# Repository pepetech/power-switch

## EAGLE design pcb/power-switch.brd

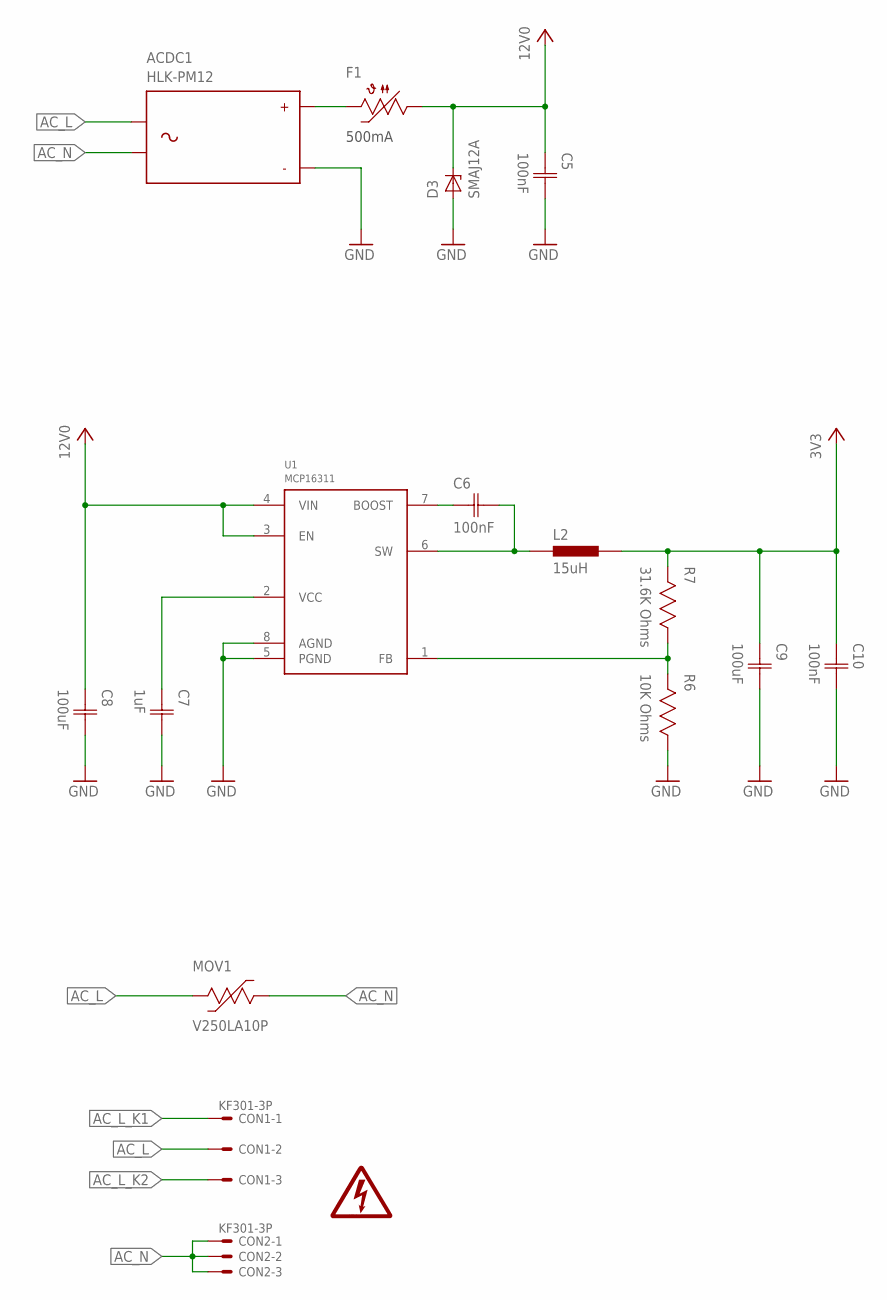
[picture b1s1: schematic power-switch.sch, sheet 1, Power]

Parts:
ACDC1: HLK-PM12
C5, C6, C10: 100nF; CAP0603
C7: 1uF; CAP0603
C8, C9: 100uF; CAP1206
CON1, CON2: KF301-3P
D3: SMAJ12A; DO214AC
F1: 500mA Hold; 1812
L2: 15uH; IND2520
LOGO1: HV_WARNING
MOV1: V250LA10P; VXXXLA10P
R6: 10K Ohms; RES0603
R7: 31.6K Ohms; RES0603
U1: MCP16311; MSOP8

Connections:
3V3: C9.1 (C1), C10.1 (C1), L2.2, R7.2; also elsewhere on the board
12V0: C5.1 (C1), C8.1 (C1), D3.C, F1.1, U1.3 (EN), U1.4 (VIN); also elsewhere on the board
AC_L: ACDC1.AC1, CON1.2, MOV1.2; also elsewhere on the board
AC_L_K1: CON1.1; also elsewhere on the board
AC_L_K2: CON1.3; also elsewhere on the board
AC_N: ACDC1.AC2, CON2.1, CON2.2, CON2.3, MOV1.1
GND: ACDC1.-VO, C5.2 (C2), C7.2 (C2), C8.2 (C2), C9.2 (C2), C10.2 (C2), D3.A, R6.1, U1.5 (PGND), U1.8 (AGND); also elsewhere on the board
unnamed: C6.2 (C2), L2.1, U1.6 (SW)
unnamed: ACDC1.+VO, F1.2
unnamed: C6.1 (C1), U1.7 (BOOST)
unnamed: C7.1 (C1), U1.2 (VCC)
unnamed: R6.2, R7.1, U1.1 (FB)

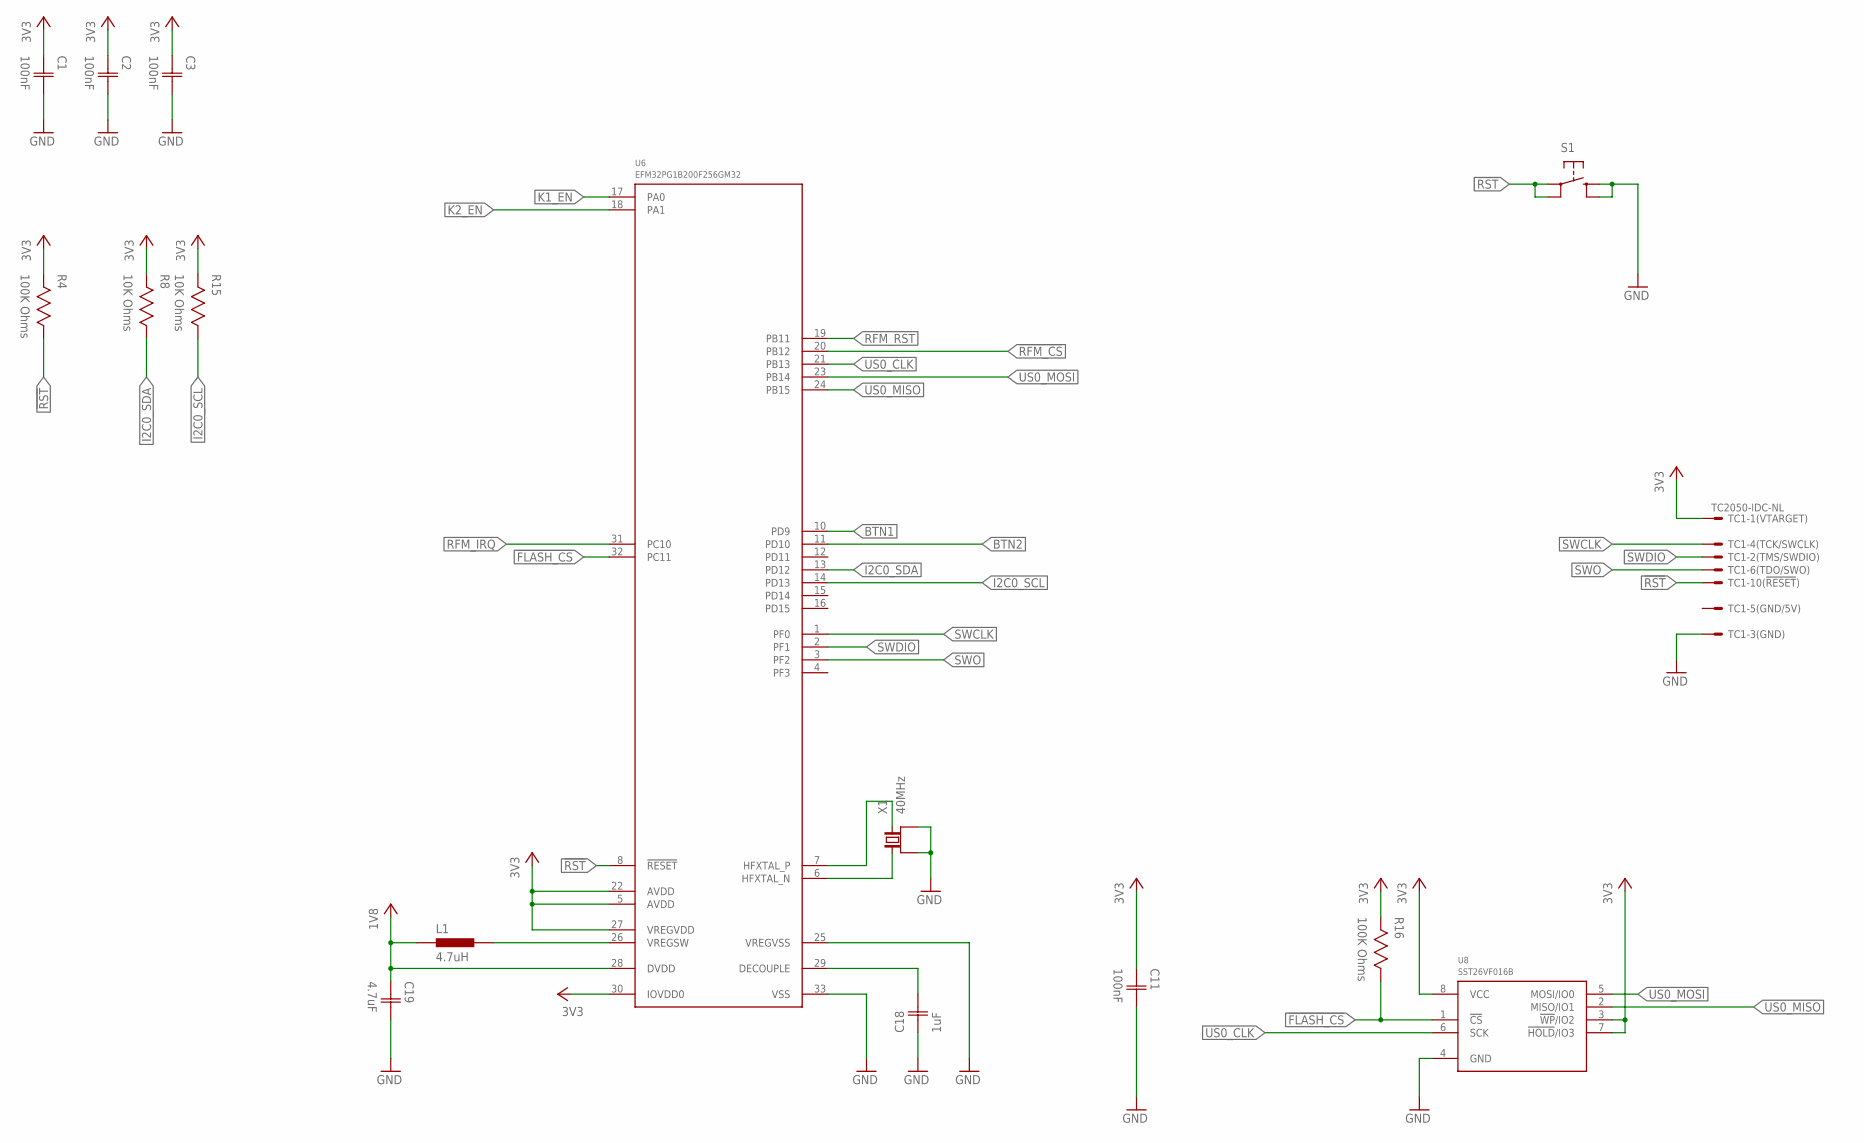
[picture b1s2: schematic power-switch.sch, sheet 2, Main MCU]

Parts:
C1, C2, C3, C11: 100nF; CAP0603
C18: 1uF; CAP0603
C19: 4.7uF; CAP0603
L1: 4.7uH; IND0603
R4, R16: 100K Ohms; RES0603
R8, R15: 10K Ohms; RES0603
S1: TAC_SWITCHSMD; TAC_SW_SMD_RESET
TC1: TC2050-IDC-NL
U6: EFM32PG1B200F256GM32; QFN32_0.5P
U8: SST26VF016B; WSOIC8
X1: 40MHz; 4-SMD-3225

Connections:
1V8: C19.1 (C1), L1.1, U6.28 (DVDD)
3V3: C1.1 (C1), C2.1 (C1), C3.1 (C1), C11.1 (C1), R4.2, R8.2, R15.2, R16.2, TC1.1, U6.5 (AVDD), U6.22 (AVDD), U6.27 (VREGVDD), U6.30 (IOVDD0), U8.3 (!WP!/IO2), U8.7 (!HOLD!/IO3), U8.8 (VCC); also elsewhere on the board
!FLASH_CS: R16.1, U6.32 (PC11), U8.1 (!CS!)
!RFM_CS: U6.20 (PB12); also elsewhere on the board
!RST: R4.1, S1.1, S1.2, TC1.10, U6.8 (!RESET)
BTN1: U6.10 (PD9); also elsewhere on the board
BTN2: U6.11 (PD10); also elsewhere on the board
GND: C1.2 (C2), C2.2 (C2), C3.2 (C2), C11.2 (C2), C18.1 (C1), C19.2 (C2), S1.3, S1.4, TC1.3, U6.25 (VREGVSS), U6.33 (VSS), U8.4 (GND), X1.1 (GND), X1.3 (GND); also elsewhere on the board
I2C0_SCL: R15.1, U6.14 (PD13); also elsewhere on the board
I2C0_SDA: R8.1, U6.13 (PD12); also elsewhere on the board
K1_EN: U6.17 (PA0); also elsewhere on the board
K2_EN: U6.18 (PA1); also elsewhere on the board
unnamed: U6.6 (HFXTAL_N), X1.2 (1)
unnamed: U6.7 (HFXTAL_P), X1.4 (2)
unnamed: L1.2, U6.26 (VREGSW)
unnamed: C18.2 (C2), U6.29 (DECOUPLE)
RFM_IRQ: U6.31 (PC10); also elsewhere on the board
RFM_RST: U6.19 (PB11); also elsewhere on the board
SWCLK: TC1.4, U6.1 (PF0)
SWDIO: TC1.2, U6.2 (PF1)
SWO: TC1.6, U6.3 (PF2)
US0_CLK: U6.21 (PB13), U8.6 (SCK); also elsewhere on the board
US0_MISO: U6.24 (PB15), U8.2 (MISO/IO1); also elsewhere on the board
US0_MOSI: U6.23 (PB14), U8.5 (MOSI/IO0); also elsewhere on the board

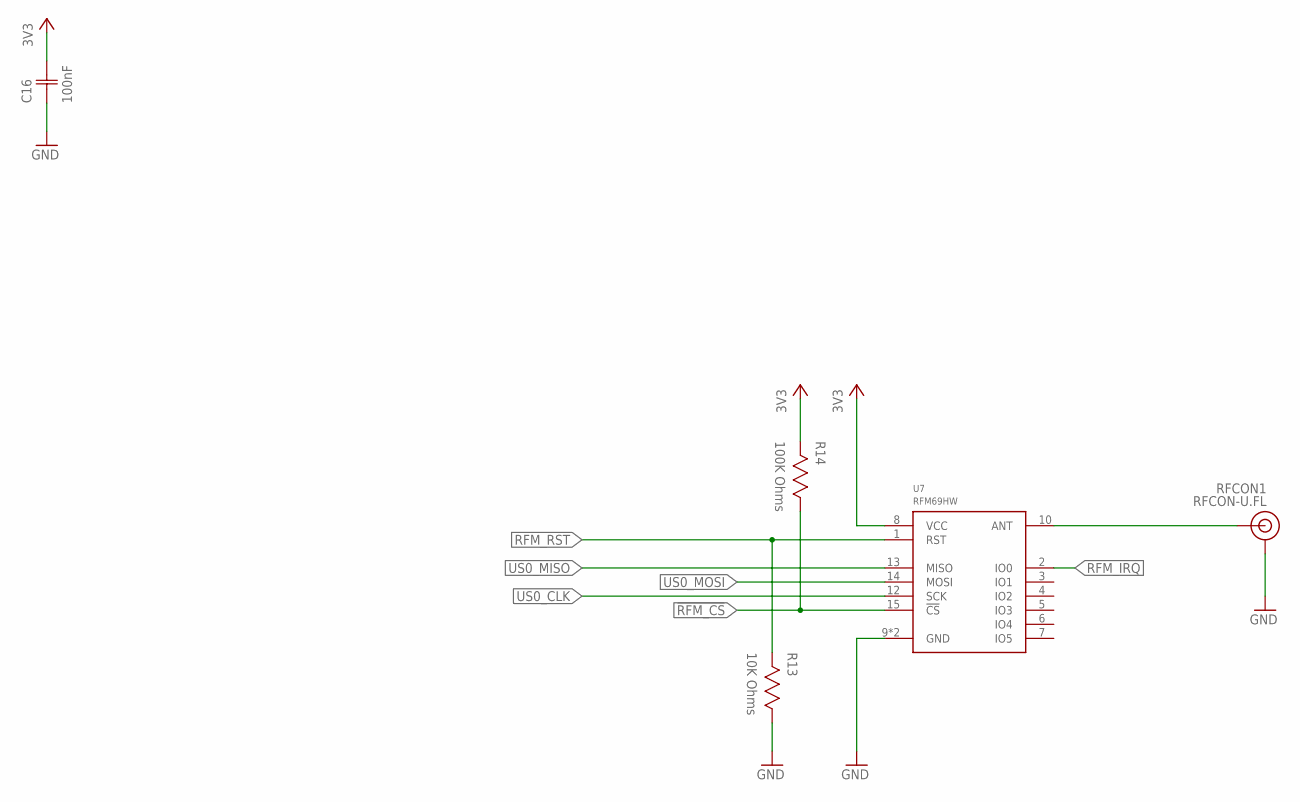
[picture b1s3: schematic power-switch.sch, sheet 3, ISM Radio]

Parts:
C16: 100nF; CAP0603
R13: 10K Ohms; RES0603
R14: 100K Ohms; RES0603
RFCON1: RFCON-U.FL; U.FL
U7: RFM69HW; RFM69XW-XXXS2

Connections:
3V3: C16.2 (C2), R14.2, U7.8 (VCC); also elsewhere on the board
!RFM_CS: R14.1, U7.15 (!CS); also elsewhere on the board
GND: C16.1 (C1), R13.1, RFCON1.P$1 (GND), RFCON1.P$2 (GND), U7.9 (GND), U7.11 (GND); also elsewhere on the board
unnamed: RFCON1.P$3 (SIGNAL), U7.10 (ANT)
RFM_IRQ: U7.2 (IO0); also elsewhere on the board
RFM_RST: R13.2, U7.1 (RST); also elsewhere on the board
US0_CLK: U7.12 (SCK); also elsewhere on the board
US0_MISO: U7.13 (MISO); also elsewhere on the board
US0_MOSI: U7.14 (MOSI); also elsewhere on the board

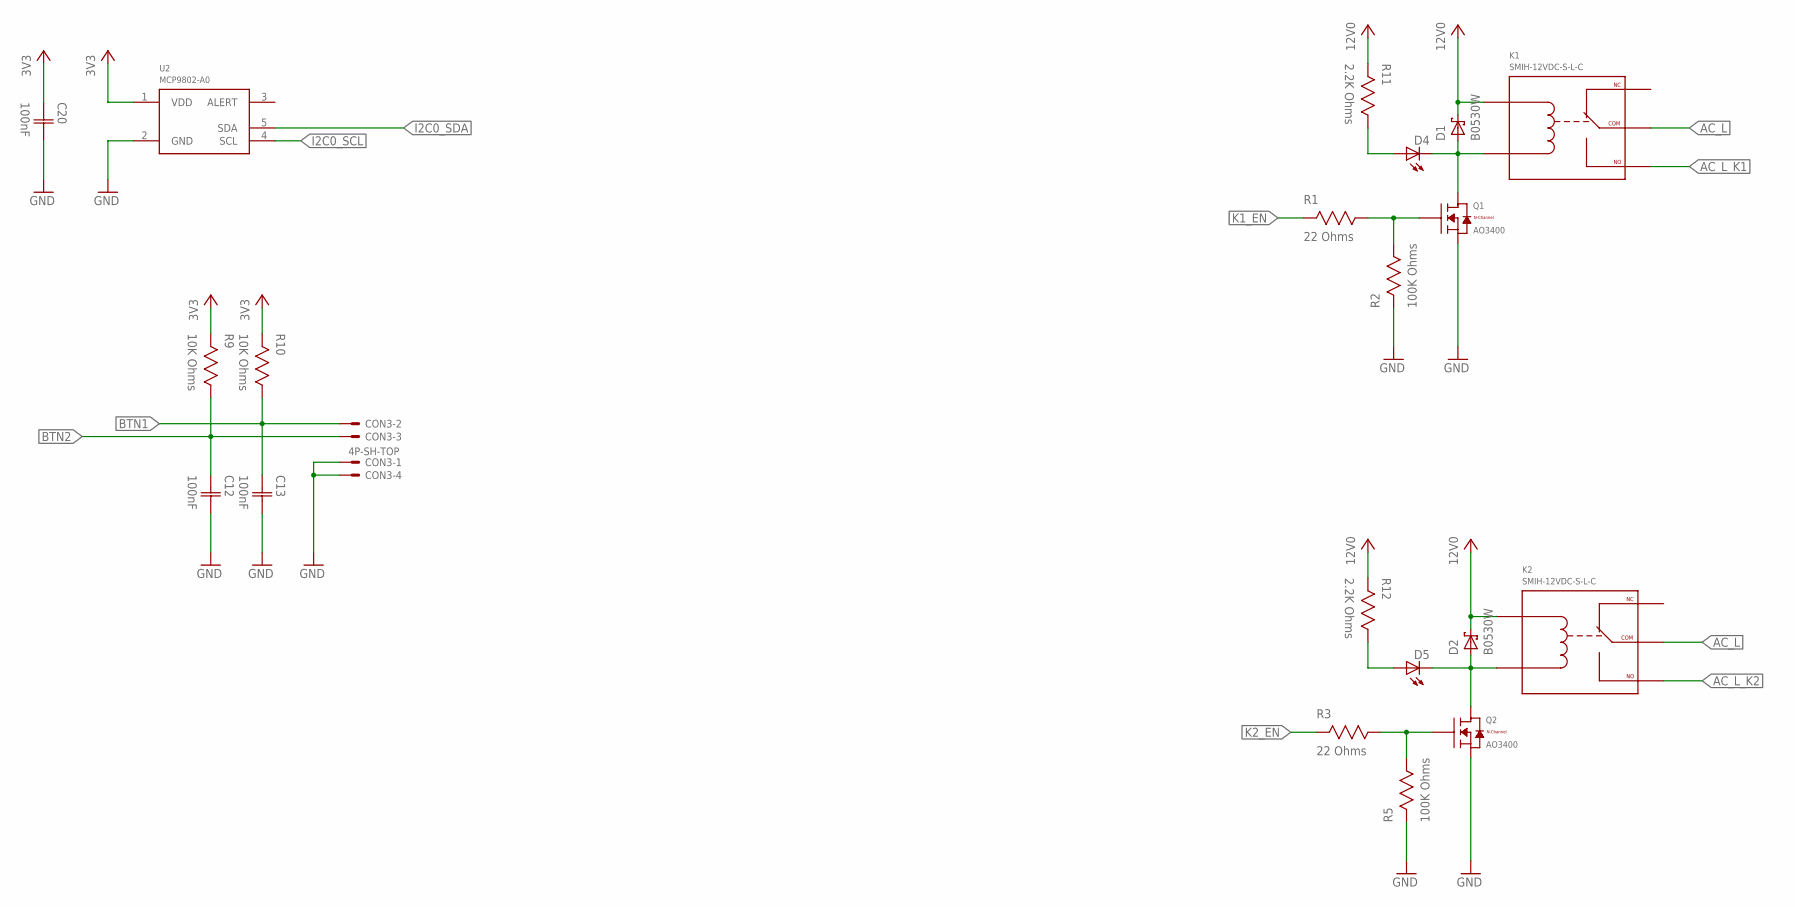
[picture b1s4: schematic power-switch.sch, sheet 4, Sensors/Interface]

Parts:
C12, C13, C20: 100nF; CAP0603
CON3: 4P-SH-TOP; SH-04-TOP
D1, D2: B0530W; SOD-123
D4, D5: LED1206; 1206
K1, K2: SMIH-12VDC-S-L-C
Q1, Q2: AO3400; SOT23
R1, R3: 22 Ohms; RES0603
R2, R5: 100K Ohms; RES0603
R9, R10: 10K Ohms; RES0603
R11, R12: 2.2K Ohms; RES0603
U2: MCP9802-A0; SOT23-5

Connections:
3V3: C20.1 (C1), R9.2, R10.2, U2.1 (VDD); also elsewhere on the board
12V0: D1.C, D2.C, K1.COIL1, K2.COIL1, R11.2, R12.2; also elsewhere on the board
AC_L: K1.COM1 (COM), K1.COM2 (COM), K2.COM1 (COM), K2.COM2 (COM); also elsewhere on the board
AC_L_K1: K1.NO1 (NO), K1.NO2 (NO); also elsewhere on the board
AC_L_K2: K2.NO1 (NO), K2.NO2 (NO); also elsewhere on the board
BTN1: C13.1 (C1), CON3.2, R10.1; also elsewhere on the board
BTN2: C12.1 (C1), CON3.3, R9.1; also elsewhere on the board
GND: C12.2 (C2), C13.2 (C2), C20.2 (C2), CON3.1, CON3.4, Q1.2 (S), Q2.2 (S), R2.2, R5.2, U2.2 (GND); also elsewhere on the board
I2C0_SCL: U2.4 (SCL); also elsewhere on the board
I2C0_SDA: U2.5 (SDA); also elsewhere on the board
K1_EN: R1.2; also elsewhere on the board
K2_EN: R3.2; also elsewhere on the board
unnamed: Q1.1 (G), R1.1, R2.1
unnamed: D1.A, D4.C, K1.COIL2, Q1.3 (D)
unnamed: Q2.1 (G), R3.1, R5.1
unnamed: D2.A, D5.C, K2.COIL2, Q2.3 (D)
unnamed: D4.A, R11.1
unnamed: D5.A, R12.1

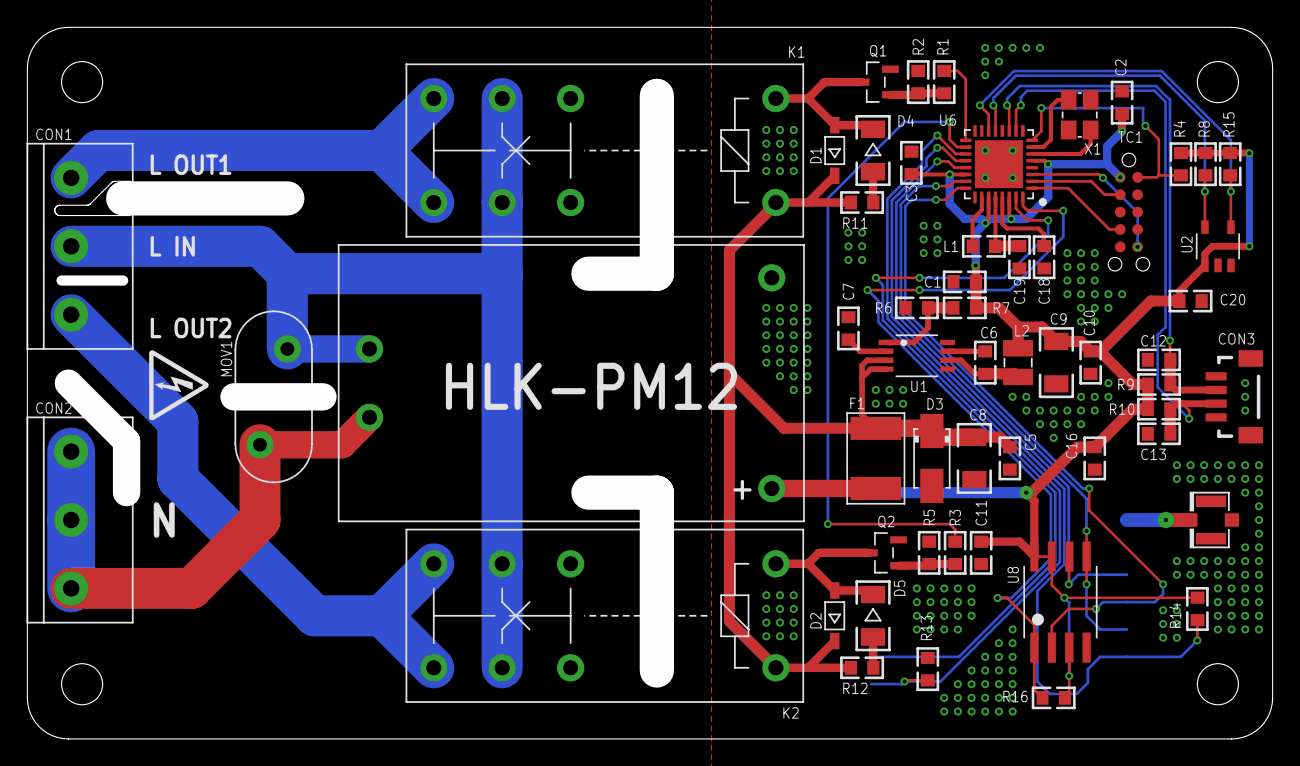
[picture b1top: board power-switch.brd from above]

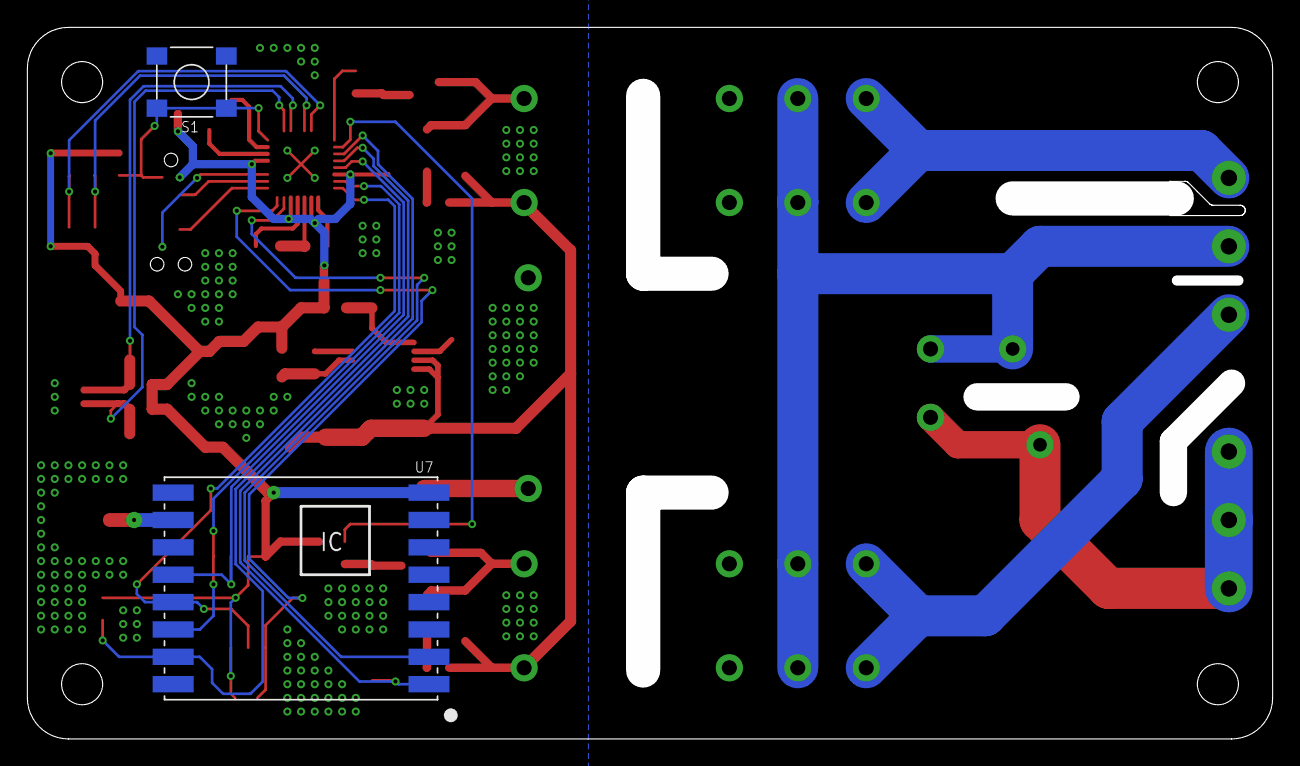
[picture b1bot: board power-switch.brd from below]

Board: 2 copper layers, 88.5 x 49.5 mm, 59 parts (2 on the bottom side), 41 nets.

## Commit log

2019-05-23 PCB Work
2019-05-25 Finished PCB
2019-05-26 Update libs
2019-07-08 Add gerbers
2019-07-28 Fix crystal package
2019-12-30 Sync library updates Add schematic PDF
2019-12-30 Update DRCs
